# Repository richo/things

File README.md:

Some things I made. I'm trying to mirror them on thingiverse but this is the
canonical location. As much as possiblee I'm including thee source (STEP and
whatever package I designed it in) but feel free to ping me.

At a high level the structure looks like;

* [airplane](airplane): Stuff I printed for my Super Decathlon. Mostly mounts for various things in the cockpit.
* [bike-stuff](bike-stuff): Stuff I printed for my bike. Much of it is bike specific (08 cbr 1000 rr), but with the .steps included it should be easy to adapt.
* [hat-adaptor](hat-adaptor): My noggin is too big for a hat I was sent so I made an adaptor for it.
* [umarells](umarells): If you know, you know.

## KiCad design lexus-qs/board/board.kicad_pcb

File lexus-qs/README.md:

lexus-qs
========

Rust project for the _Arduino Nano_.

## Build Instructions
1. Install prerequisites as described in the [`avr-hal` README] (`avr-gcc`, `avr-libc`, `avrdude`, [`ravedude`]).

2. Run `cargo build` to build the firmware.

3. Run `cargo run` to flash the firmware to a connected board.  If `ravedude`
   fails to detect your board, check its documentation at
   <https://crates.io/crates/ravedude>.

4. `ravedude` will open a console session after flashing where you can interact
   with the UART console of your board.

[`avr-hal` README]: https://github.com/Rahix/avr-hal#readme
[`ravedude`]: https://crates.io/crates/ravedude

## License
Licensed under either of

 - Apache License, Version 2.0
   ([LICENSE-APACHE](LICENSE-APACHE) or <http://www.apache.org/licenses/LICENSE-2.0>)
 - MIT license
   ([LICENSE-MIT](LICENSE-MIT) or <http://opensource.org/licenses/MIT>)

at your option.

## Contribution
Unless you explicitly state otherwise, any contribution intentionally submitted
for inclusion in the work by you, as defined in the Apache-2.0 license, shall
be dual licensed as above, without any additional terms or conditions.

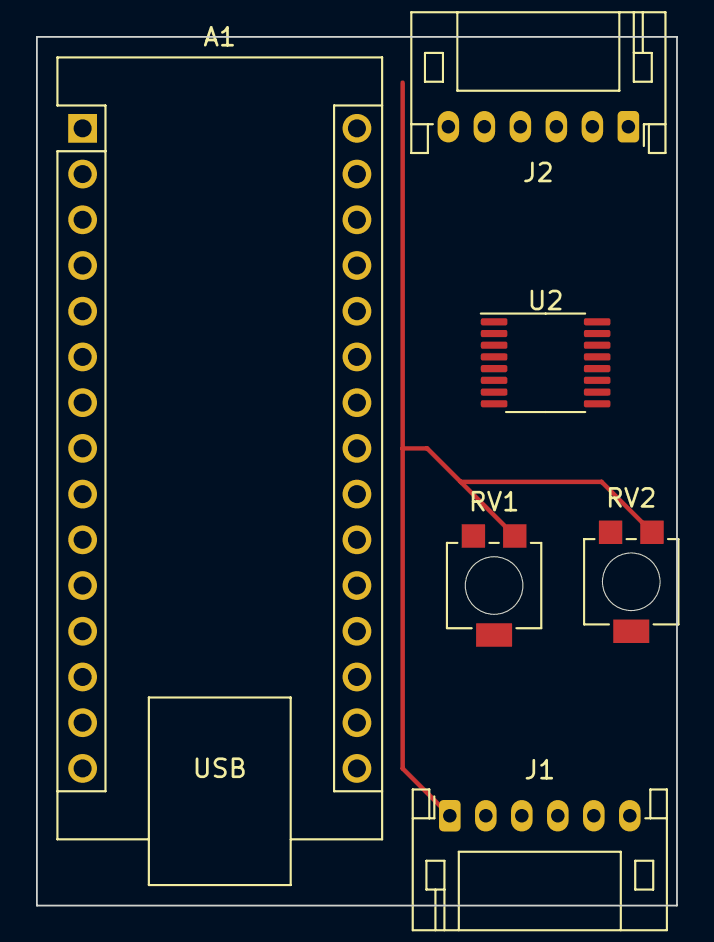
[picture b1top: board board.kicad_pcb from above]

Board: 2 copper layers, 35.6 x 48.3 mm, 6 parts (0 on the bottom side), 13 nets.

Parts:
A1: Arduino_Nano_v3.x; Arduino_Nano
J1, J2: Conn_01x06_Socket; JST_PH_S6B-PH-K_1x06_P2.00mm_Horizontal
RV1, RV2: R_Potentiometer_Trim; Potentiometer_Bourns_3314R-1_Vertical_Hole
U2: ADG729; TSSOP-16_4.4x5mm_P0.65mm

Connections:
unnamed: A1.23 (A4), U2.1 (SCL)
unnamed: A1.24 (A5), U2.3 (SDA)
unnamed: A1.8 (D5), J2.1
unnamed: A1.9 (D6), J2.3
unnamed: A1.10 (D7), J2.2
unnamed: A1.30 (VIN), J1.1, RV1.1, RV2.1, U2.14 (VDD)
unnamed: A1.29 (GND), J1.2, RV1.3, RV2.3, U2.15 (GND)
unnamed: J1.3, U2.4 (S1A)
unnamed: J1.4, U2.13 (S1B)
unnamed: J1.5, U2.8 (DA)
unnamed: J1.6, U2.9 (DB)
unnamed: RV2.2, U2.5 (S2A), U2.12 (S2B)
unnamed: RV1.2, U2.6 (S3A), U2.11 (S3B)

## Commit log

2020-12-07 Some spacers I made for my cbr1000rr to drop the forks down
    You can easily tweak the scad file to amke any size you want
2020-12-07 Some umarells honeslty at this point who knows
2020-12-09 Start aggregating bike stuff
2020-12-09 Add my mirror blockoffs
2020-12-09 Add that hat adaptor I made
2020-12-09 Add thee shift p2 mount I madee
2020-12-09 Add the flapper blockoffs I made
2020-12-09 Add th echain jig i madee
2020-12-09 Add the bar end spacers I made
2020-12-09 Add an older attmpt at the shift p2 mount
    This one is not as clean but doesn't require remeoving the backplate
2020-12-09 OAdd my PCV tray
2020-12-09 Add some airplane stuff I designed
2020-12-09 Add the mount I made for my airplane
2020-12-09 License CC BY
2020-12-09 Update the readme
2020-12-10 Add my flysight mounts for tfx
2020-12-13 Add a switchblock I designed
2020-12-23 Add the firmware for my switchblock
2021-01-02 Add new switchblock version
2021-01-10 Add this airfoil geometry
2021-01-10 Add a proto from fusion
2021-01-10 Some work I did on windows
2021-01-12 Close up 3806
2021-01-12 close up 5806
2021-01-12 Add naca3806
2021-01-12 Add more naca madness
2021-01-12 add notes
2021-01-16 Jotting down more notes
2021-01-16 Add a scan of my sidepanel
2021-01-16 raw sca
2021-01-16 WIP of my carved down sidepanel
2021-01-16 Smallest sidepanel i could get
2021-01-23 Some notes on the sidebody mesh
2021-01-23 Scale the sidepanel up pretty closes to real scale
2021-01-23 Maybe another 10x is the right dimensions, I'm praying this is just a cm/mm thing
2021-01-24 add winglet
2021-01-24 Attempted winglet cut with Blender
2021-01-24 add my smaller sidepanel and it's lowpoly cousin
2021-01-25 Add solidworks prats for winglets
2021-01-30 add a kinect scan of the bike
2021-02-06 Add my stratux mount
2021-02-06 Update stratux mount
2021-02-06 Added my inspection late cover
2021-02-08 Add my phone charger :wq
2023-02-26 Miight as well keep it I guess
2023-02-26 initial import
2023-02-26 Looks like a working ish impl
2023-02-26 So fucking broken
2023-02-26 Bigger refactor
2023-02-27 Able to write text on a display!
2023-02-27 Relay clickies
2023-03-01 Builds without warnings!
2023-03-01 Refactor a bunch of the button handling
2023-03-01 Include the number of millis
2023-03-01 Add millis support
2023-03-01 Finer grained millis
2023-03-01 Millis actually work and have a shitty test
2023-03-01 Helper
2023-03-01 Show progress over serial for backflushing
2023-03-01 Toyed around with more brew methods
2023-03-01 Some trait fuckery
2023-03-01 Make backflushing just a kind of brew
2023-03-01 Add prenifuse brew
2023-03-01 Migrate everything to the new result struct
2023-03-01 Add support for showing things on the screen
2023-03-02 Counting up works
2023-03-02 Example that counts up
2023-03-02 String formatting is less jank now
2023-03-02 Start trimming
2023-03-02 More cleaning up
2023-03-02 Reset the title line
2023-03-02 POC of interrupts for buttons
2023-03-02 Cool beans!
    We have learned that we can only use interrupts on these two pins.
    Fabulous.
2023-03-02 Make it harder to accidentally start a second brew
2023-03-02 Clean up some warnings
2023-03-02 Respect a standby period
2023-03-02 Dummy for screen testing, show backflush when that's what we're doing
2023-03-03 This starts migrating to a two button thing
2023-03-03 Able to select different brews
2023-03-03 Rename the switches
2023-03-03 Only stop on the cancel button
2023-03-03 Make vtables work but I dunno if it's better
2023-03-05 Fix some brews not using helpers and institutionalise how to turn them off
2023-03-05 Use the new api that allows for disabling
2023-03-05 Make the counters a little smarter
2023-03-05 Display the shot time
2023-03-05 Fix a typo in the straight brew
2023-03-05 Show the time when we're done
2023-03-06 dd a repro brew
2023-03-06 Cleanups
2023-03-06 Hack on the thing to reinit maybe
2023-03-06 Debug brewing
2023-03-06 Write a string formatting library they said it'll be fun they said
2023-03-06 Make myself a note
2023-03-06 Fix timing
2023-03-06 Show no time if we ran to conclusion
2023-03-06 Rewrite some string formatting
2023-03-06 Show done when it finishes successfully
2023-03-06 Trim down the firmware
2023-03-06 Document some things
2023-03-06 No warnings!
2023-03-07 PoC to have both switches tied up to the interrupts
2023-03-07 Migrate everything to interrupts
2023-03-07 Back to no warnings
2023-03-07 try?
2023-03-07 Reset the display when we're paused on the homescreen
2023-03-07 Show the version on startup
2023-03-07 Show a nicer version
2023-03-07 Works better with the build script
2023-03-07 Bump version because things are kinda stable
2023-03-07 Slightly nicer display of the version
2023-03-13 Whitespace
2023-03-13 Debounce buttons
2023-03-13 Add valve open test
2023-03-13 Only cancel stops brewing
2023-03-13 Fix my whoopsies
2023-06-19 Don't wait for the last backflush
2023-10-01 Redraw the screen when the pump comes on
2023-10-01 Teach the machine to flush after brewing
2024-06-26 STart a rewrite
2024-06-26 Brought in a working arduino nano thing to port from
2024-06-27 First attempt at porting the firmware
2024-06-27 Wooo I rewrote the firmwars
2024-07-04 Mostly working again
2024-11-16 Add template
2024-11-16 Flipping through channels
2024-11-16 Proto of holding a value
2024-11-16 First working protoyype
2024-11-16 Think this might work
2024-11-16 Slightly longer delay
2024-11-16 Add most of the plumbing for a shift cut as well
2024-11-16 Start tidying up
2024-11-26 Weeee working debounce
2024-11-29 WIP on the board
2024-12-08 Add gitignore
2024-12-08 Got it to production ready!
2024-12-13 Update board for my goofd
2024-12-13 Deal with not necessarily knowing where the mux will end up
